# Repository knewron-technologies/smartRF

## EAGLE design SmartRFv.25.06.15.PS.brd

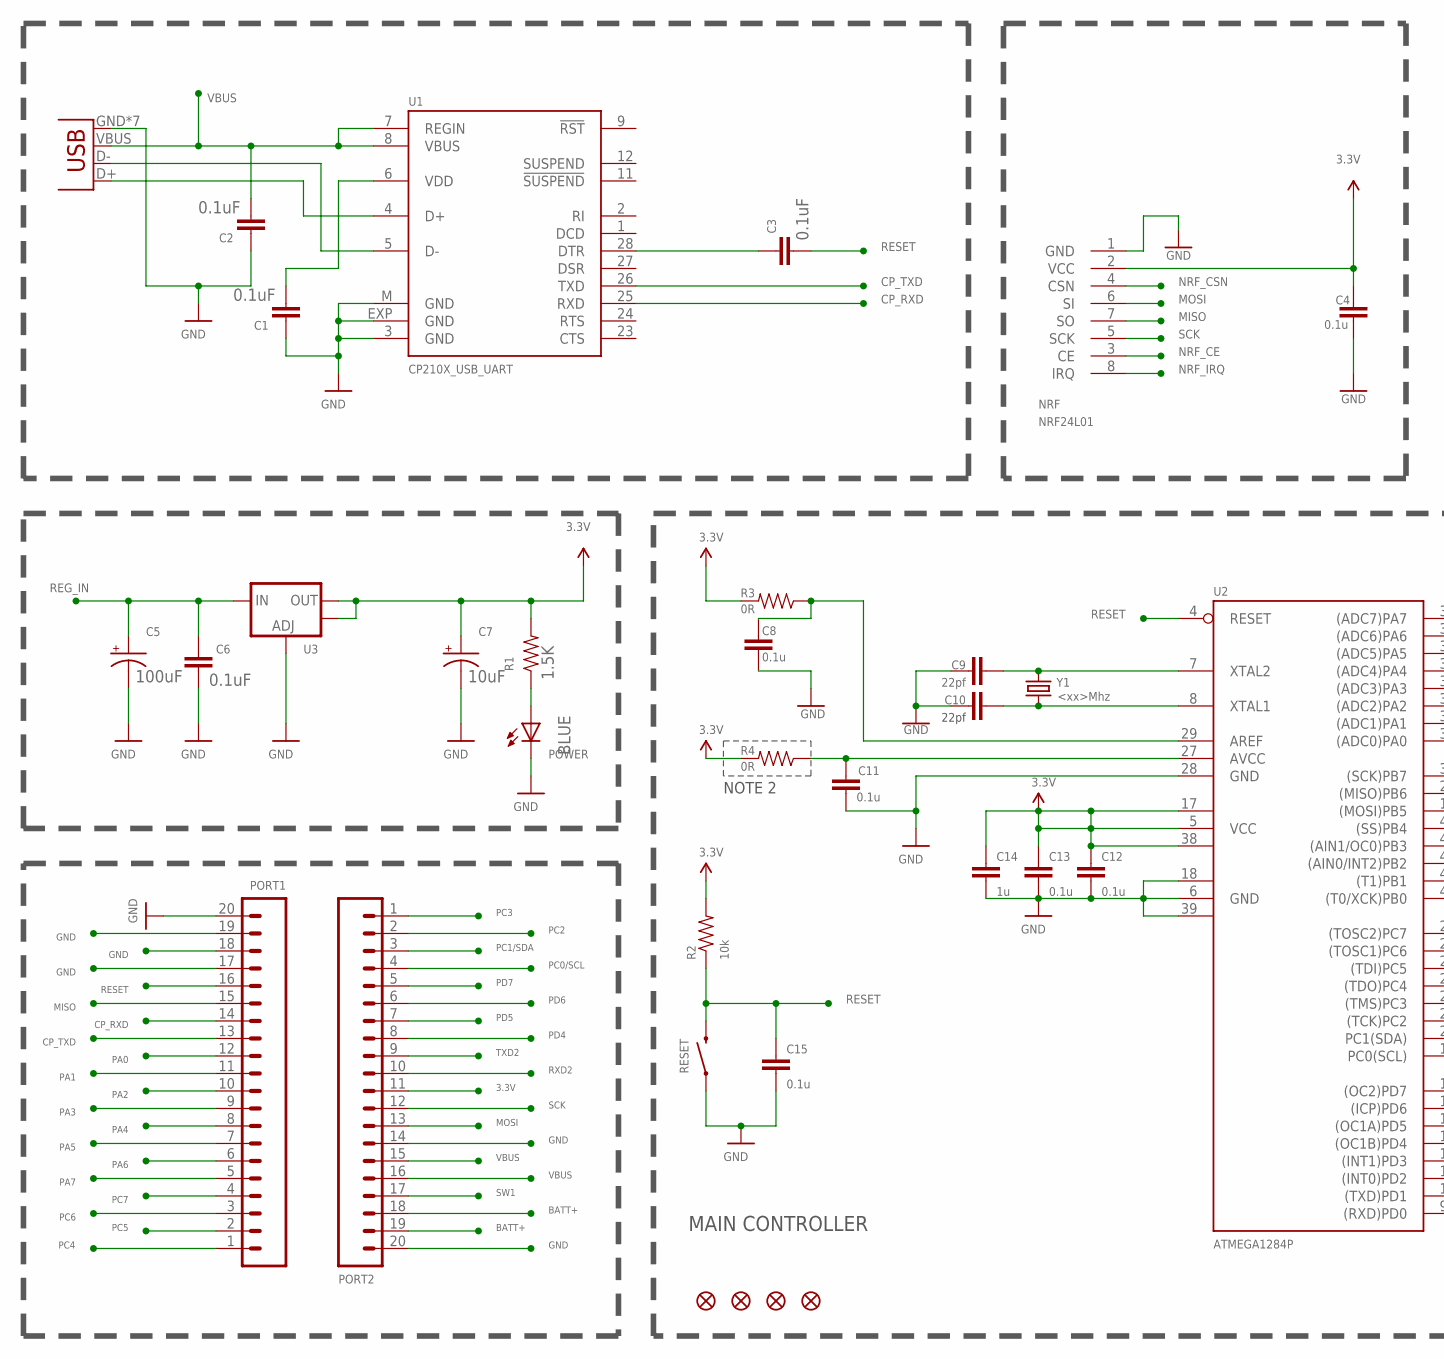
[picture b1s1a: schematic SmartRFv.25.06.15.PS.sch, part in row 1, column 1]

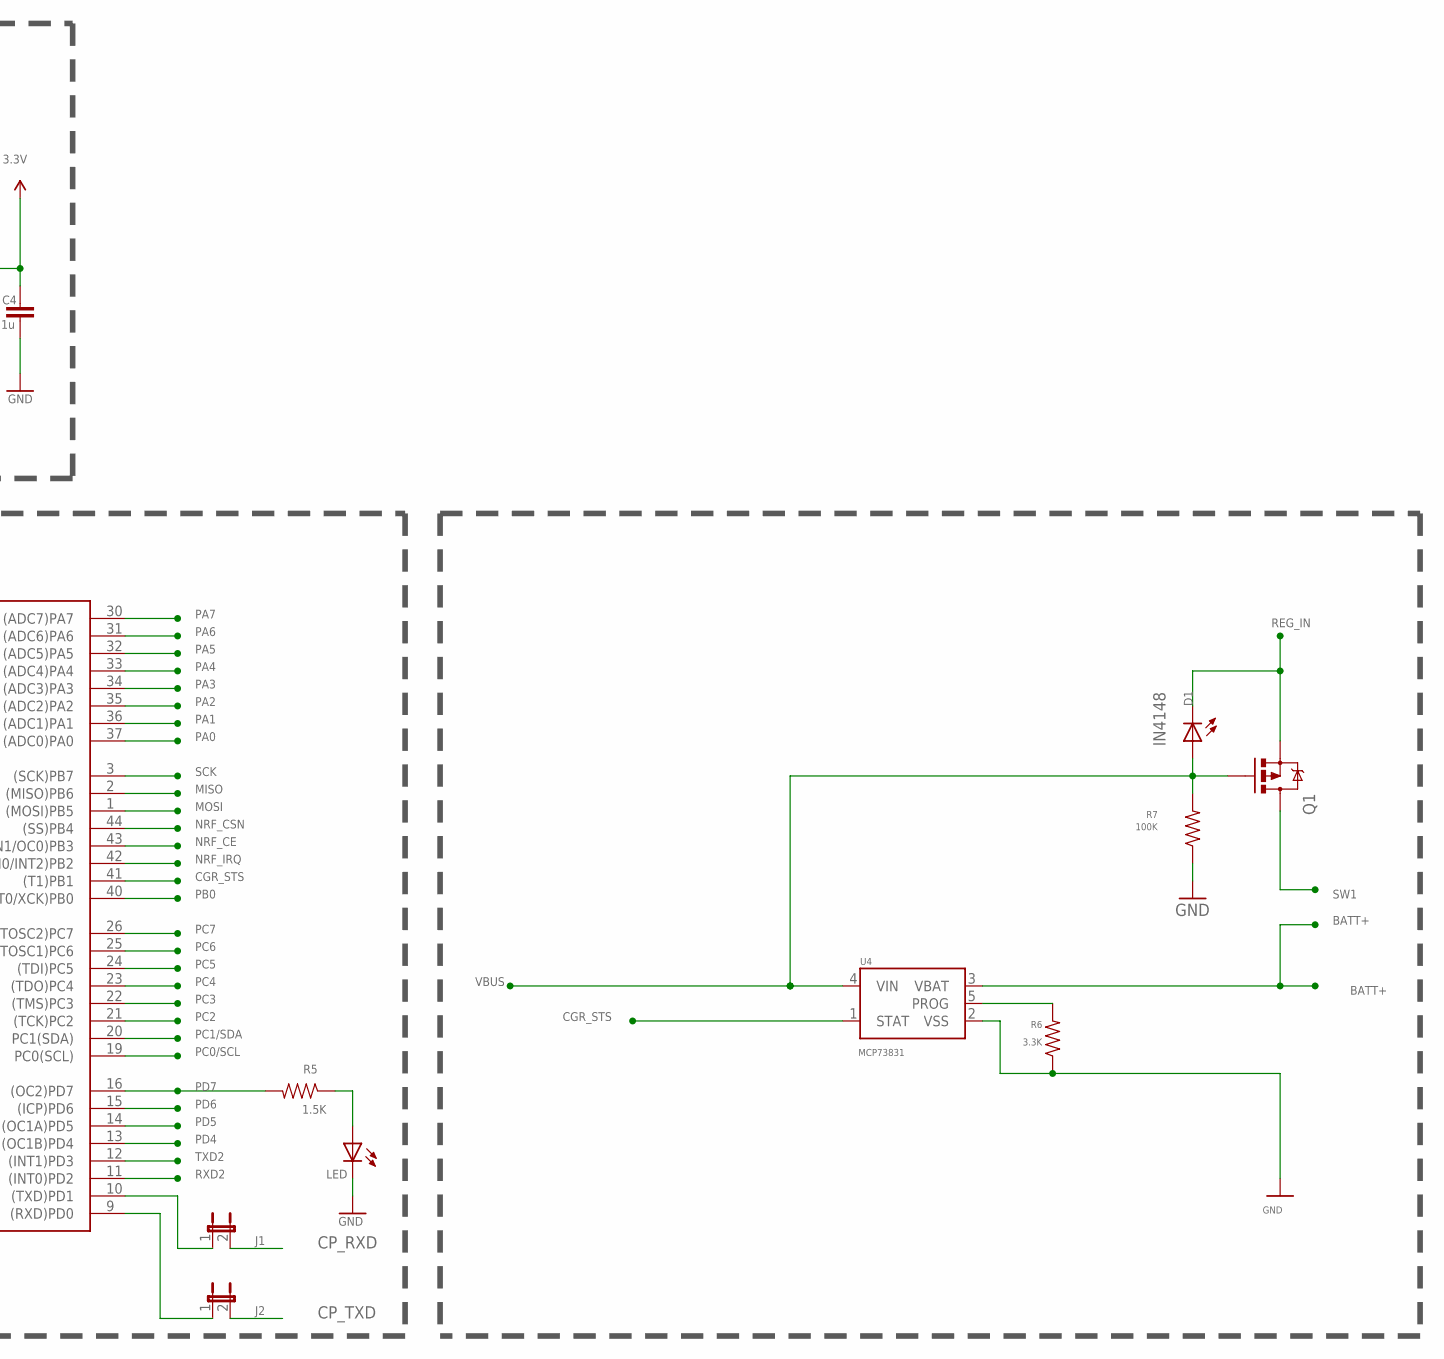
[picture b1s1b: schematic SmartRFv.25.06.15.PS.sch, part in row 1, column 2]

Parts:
C1, C2, C3, C6: 0.1uF; 0805
C4, C8, C11, C12, C13, C15: 0.1u; 0805
C5: 100uF; EIA3216-KIT
C7: 10uF; EIA3216-KIT
C9, C10: 22pf; 0805
C14: 1u; 0805
D1: IN4148; LED-1206
FID1, FID2, FID3, FID4: FIDUCIAL1X2; FIDUCIAL-1X2
J1, J2: JUMPER-2SMD-NC; SJ_2S
LED: LED; LED-0805
NRF: NRF2401; MFR_PN NRF24L01
PORT1, PORT2: M20; 1X20
POWER: BLUE; LED-0805
Q1: MOSFET-PCHANNELSMD; SOT23-3
R1, R5: 1.5K; 0805
R2: 10k; 0805
R3, R4: 0R; 0805
R6: 3.3K; 0805
R7: 100K; 0805
RESET: SWITCH-MOMENTARY-2-SMD-1101NE; TACTILE-SWITCH-1101NE
U1: CP210X_USB_UART; MLP28
U2: MEGA32-A; TQFP44; MPN ATMEGA1284P
U3: V_REG_LM1117SOT223; SOT223
U4: MCP73831; SOT23-5
USB: USB-MICROB
Y1: <xx>Mhz; CRYSTAL-SMD-5X3

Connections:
3.3V: C4.2, C7.A (+), C12.1, C13.1, C14.1, NRF.2 (VCC), PORT2.11, R1.2, R2.2, R3.2, R4.2, U2.5 (VCC), U2.17 (VCC1), U2.38 (VCC2), U3.2 (OUT), U3.4 (OUT)
BATT+: PORT2.18, PORT2.19, U4.3 (VBAT)
CGR_STS: U2.41 ((T1)PB1), U4.1 (STAT)
CP_RXD: J1.2, PORT1.14, U1.25 (RXD)
CP_TXD: J2.2, PORT1.13, U1.26 (TXD)
GND: C1.1, C2.1, C4.1, C5.C (-), C6.2, C7.C (-), C8.2, C9.1, C10.1, C11.2, C12.2, C13.2, C14.2, C15.2, LED.2 (C), NRF.1 (GND), PORT1.17, PORT1.18, PORT1.19, PORT1.20, PORT2.14, PORT2.20, POWER.2 (C), R6.1, R7.1, RESET.P$1 (1), U1.3 (GND), U1.EXP (GND), U1.M (GND), U2.6 (GND), U2.18 (GND1), U2.28 (GND), U2.39 (GND2), U3.1 (ADJ), U4.2 (VSS), USB.GND, USB.MT1 (GND), USB.MT2 (GND), USB.MT3 (GND), USB.MT4 (GND), USB.P$1 (GND), USB.P$2 (GND)
MISO: NRF.7 (SO), PORT1.15, U2.2 ((MISO)PB6)
MOSI: NRF.6 (SI), PORT2.13, U2.1 ((MOSI)PB5)
unnamed: C9.2, U2.7 (XTAL2), Y1.3 (2)
unnamed: C10.2, U2.8 (XTAL1), Y1.1
unnamed: J1.1, U2.10 ((TXD)PD1)
unnamed: C11.1, R4.1, U2.27 (AVCC)
unnamed: U1.5 (D-), USB.D-
unnamed: C3.1, U1.28 (DTR)
unnamed: POWER.1 (A), R1.1
unnamed: U1.4 (D+), USB.D+
unnamed: J2.1, U2.9 ((RXD)PD0)
unnamed: C8.1, R3.1, U2.29 (AREF)
unnamed: LED.1 (A), R5.1
unnamed: R6.2, U4.5 (PROG)
NRF_CE: NRF.3 (CE), U2.43 ((AIN1/OC0)PB3)
NRF_CSN: NRF.4 (CSN), U2.44 ((SS)PB4)
NRF_IRQ: NRF.8 (IRQ), U2.42 ((AIN0/INT2)PB2)
PA0: PORT1.12, U2.37 ((ADC0)PA0)
PA1: PORT1.11, U2.36 ((ADC1)PA1)
PA2: PORT1.10, U2.35 ((ADC2)PA2)
PA3: PORT1.9, U2.34 ((ADC3)PA3)
PA4: PORT1.8, U2.33 ((ADC4)PA4)
PA5: PORT1.7, U2.32 ((ADC5)PA5)
PA6: PORT1.6, U2.31 ((ADC6)PA6)
PA7: PORT1.5, U2.30 ((ADC7)PA7)
PB0: U2.40 ((T0/XCK)PB0)
PC0/SCL: PORT2.4, U2.19 (PC0(SCL))
PC1/SDA: PORT2.3, U2.20 (PC1(SDA))
PC2: PORT2.2, U2.21 ((TCK)PC2)
PC3: PORT2.1, U2.22 ((TMS)PC3)
PC4: PORT1.1, U2.23 ((TDO)PC4)
PC5: PORT1.2, U2.24 ((TDI)PC5)
PC6: PORT1.3, U2.25 ((TOSC1)PC6)
PC7: PORT1.4, U2.26 ((TOSC2)PC7)
PD4: PORT2.8, U2.13 ((OC1B)PD4)
PD5: PORT2.7, U2.14 ((OC1A)PD5)
PD6: PORT2.6, U2.15 ((ICP)PD6)
PD7: PORT2.5, R5.2, U2.16 ((OC2)PD7)
REG_IN: C5.A (+), C6.1, D1.C, Q1.2 (S), U3.3 (IN)
RESET: C3.2, C15.1, PORT1.16, R2.1, RESET.P$2 (2), U2.4 (RESET)
RXD2: PORT2.10, U2.11 ((INT0)PD2)
SCK: NRF.5 (SCK), PORT2.12, U2.3 ((SCK)PB7)
SW1: PORT2.17, Q1.3 (D)
TXD2: PORT2.9, U2.12 ((INT1)PD3)
VBUS: C2.2, D1.A, PORT2.15, PORT2.16, Q1.1 (G), R7.2, U1.7 (REGIN), U1.8 (VBUS), U4.4 (VIN), USB.VBUS
VDD: C1.2, U1.6 (VDD)

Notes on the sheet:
NOTE 2
MAIN CONTROLLER

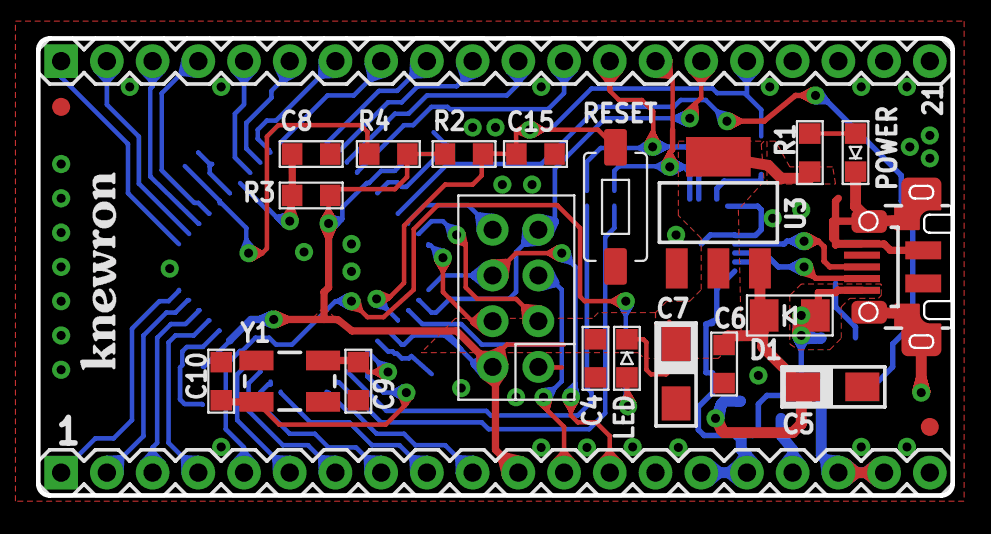
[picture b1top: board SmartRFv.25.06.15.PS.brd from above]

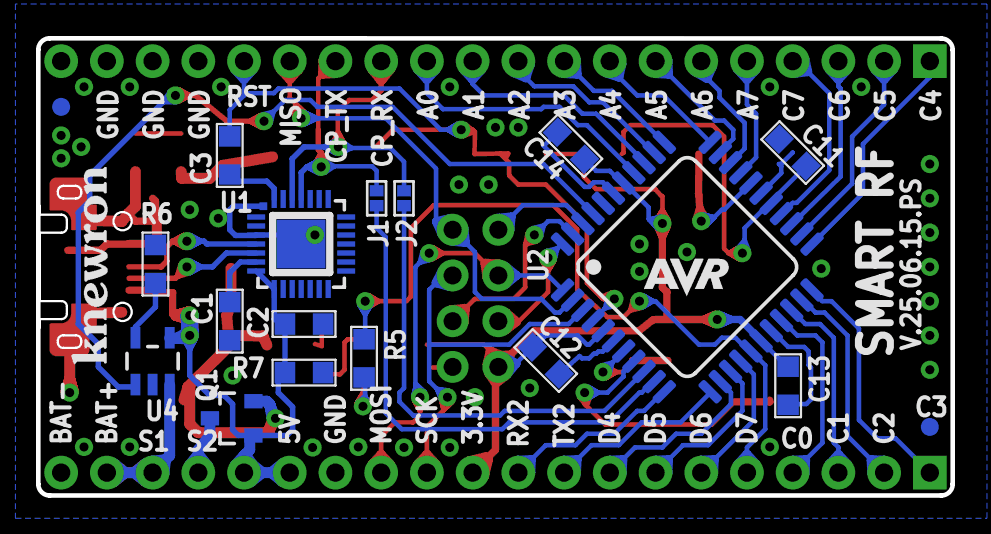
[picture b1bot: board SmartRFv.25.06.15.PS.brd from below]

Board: 2 copper layers, 50.8 x 25.4 mm, 45 parts (20 on the bottom side), 51 nets.

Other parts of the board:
U$1, U$2: KNEWRON-NAME3
U$3: AVR-SYMBOL

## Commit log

2015-11-03 license added
2015-11-03 eagle files added
2015-11-03 user doc added
2015-11-03 image files added
2015-11-03 removed batch file
2016-08-18 circuit diagram image added

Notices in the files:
parts and their libraries:
SparkFun-PowerIC: Licensing: CC v3.0 Share-Alike You are welcome to use this library for commercial purposes.
SparkFun-Connectors: Licensing: Creative Commons ShareAlike 4.0 International - https://creativecommons.org/licenses/by-sa/4.0
Knewron: (c) 2012
